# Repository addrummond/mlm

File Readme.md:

# Mimimalist Light Meter

## User manual

The user manual is [here](https://github.com/addrummond/mlm/blob/master/manual/manual.md).

## Overview

This is a simple ambient light meter using a Liteon LTR-303ALS light sensor and
an EFM32 Tiny Gecko ARM microcontroller. It is powered by a single CR2032 coin cell.
The firmware is written in C and the PCB is designed using KiCad. Readings are
displayed using a circle of 24 LEDs, with two additional LEDs indicating ±⅓ stop
adjustments. The user interface consists of three touch sensitive pads.

The goal of the project is to make available a simple, compact and inexpensive
light meter suitable for analogue photography. 

Dimensions: 87×56x7.5mm

The bottom side of the PCB (the side with no components mounted) is intended to
be used as the top panel of the case. This works best with a standard 1.6mm PCB
thickness.

The case is designed for 3D printing. It's best to use multi-jet fusion, as PLA
and ABS are usually not very light tight. (You could use PLA/ABS and then paint
the inside of the case black.) The STL file and Fusion 360 design for the case
are in the `case` directory. The PCB attaches to the case using five M1.6 4mm
countersunk screws. The dimples under the LEDs should be painted white and then
given a gloss varnish. A 10×10×2mm piece of transparent acrylic should be glued
in place over the sensor window. (If you don't add this, adjust
`WINDOW_ATTENUATION_STOPS` in `config.h`.)

The device functions as a reflective light meter. The same design could be
adapted for a spot meter or incident light meter by placing a lens or diffuser
over the sensor.

The LTR-303ALS integrates over a period of 50-400ms, which is far too long for
effective flash metering. A different design would therefore be required for
this purpose (probably using a discrete photodiode).

## Build notes

See `firmware/Readme.md` for notes on the dev toolchain.

Note that a recent (as of June 2020) development version of KiCad will be
required to open the board and schema files. Version 5.99.0-3928-g3c8396cd0 is
known to work. Each component in the schematic has a `MAN` (manufacturer) and
`MPN` (manufacturer part number) property.

I recommend using the [interactive BOM](https://github.com/openscopeproject/InteractiveHtmlBom) plugin for KiCad to aid manual placement of components.

## Known issue

* LEDs a little dim in bright daylight.

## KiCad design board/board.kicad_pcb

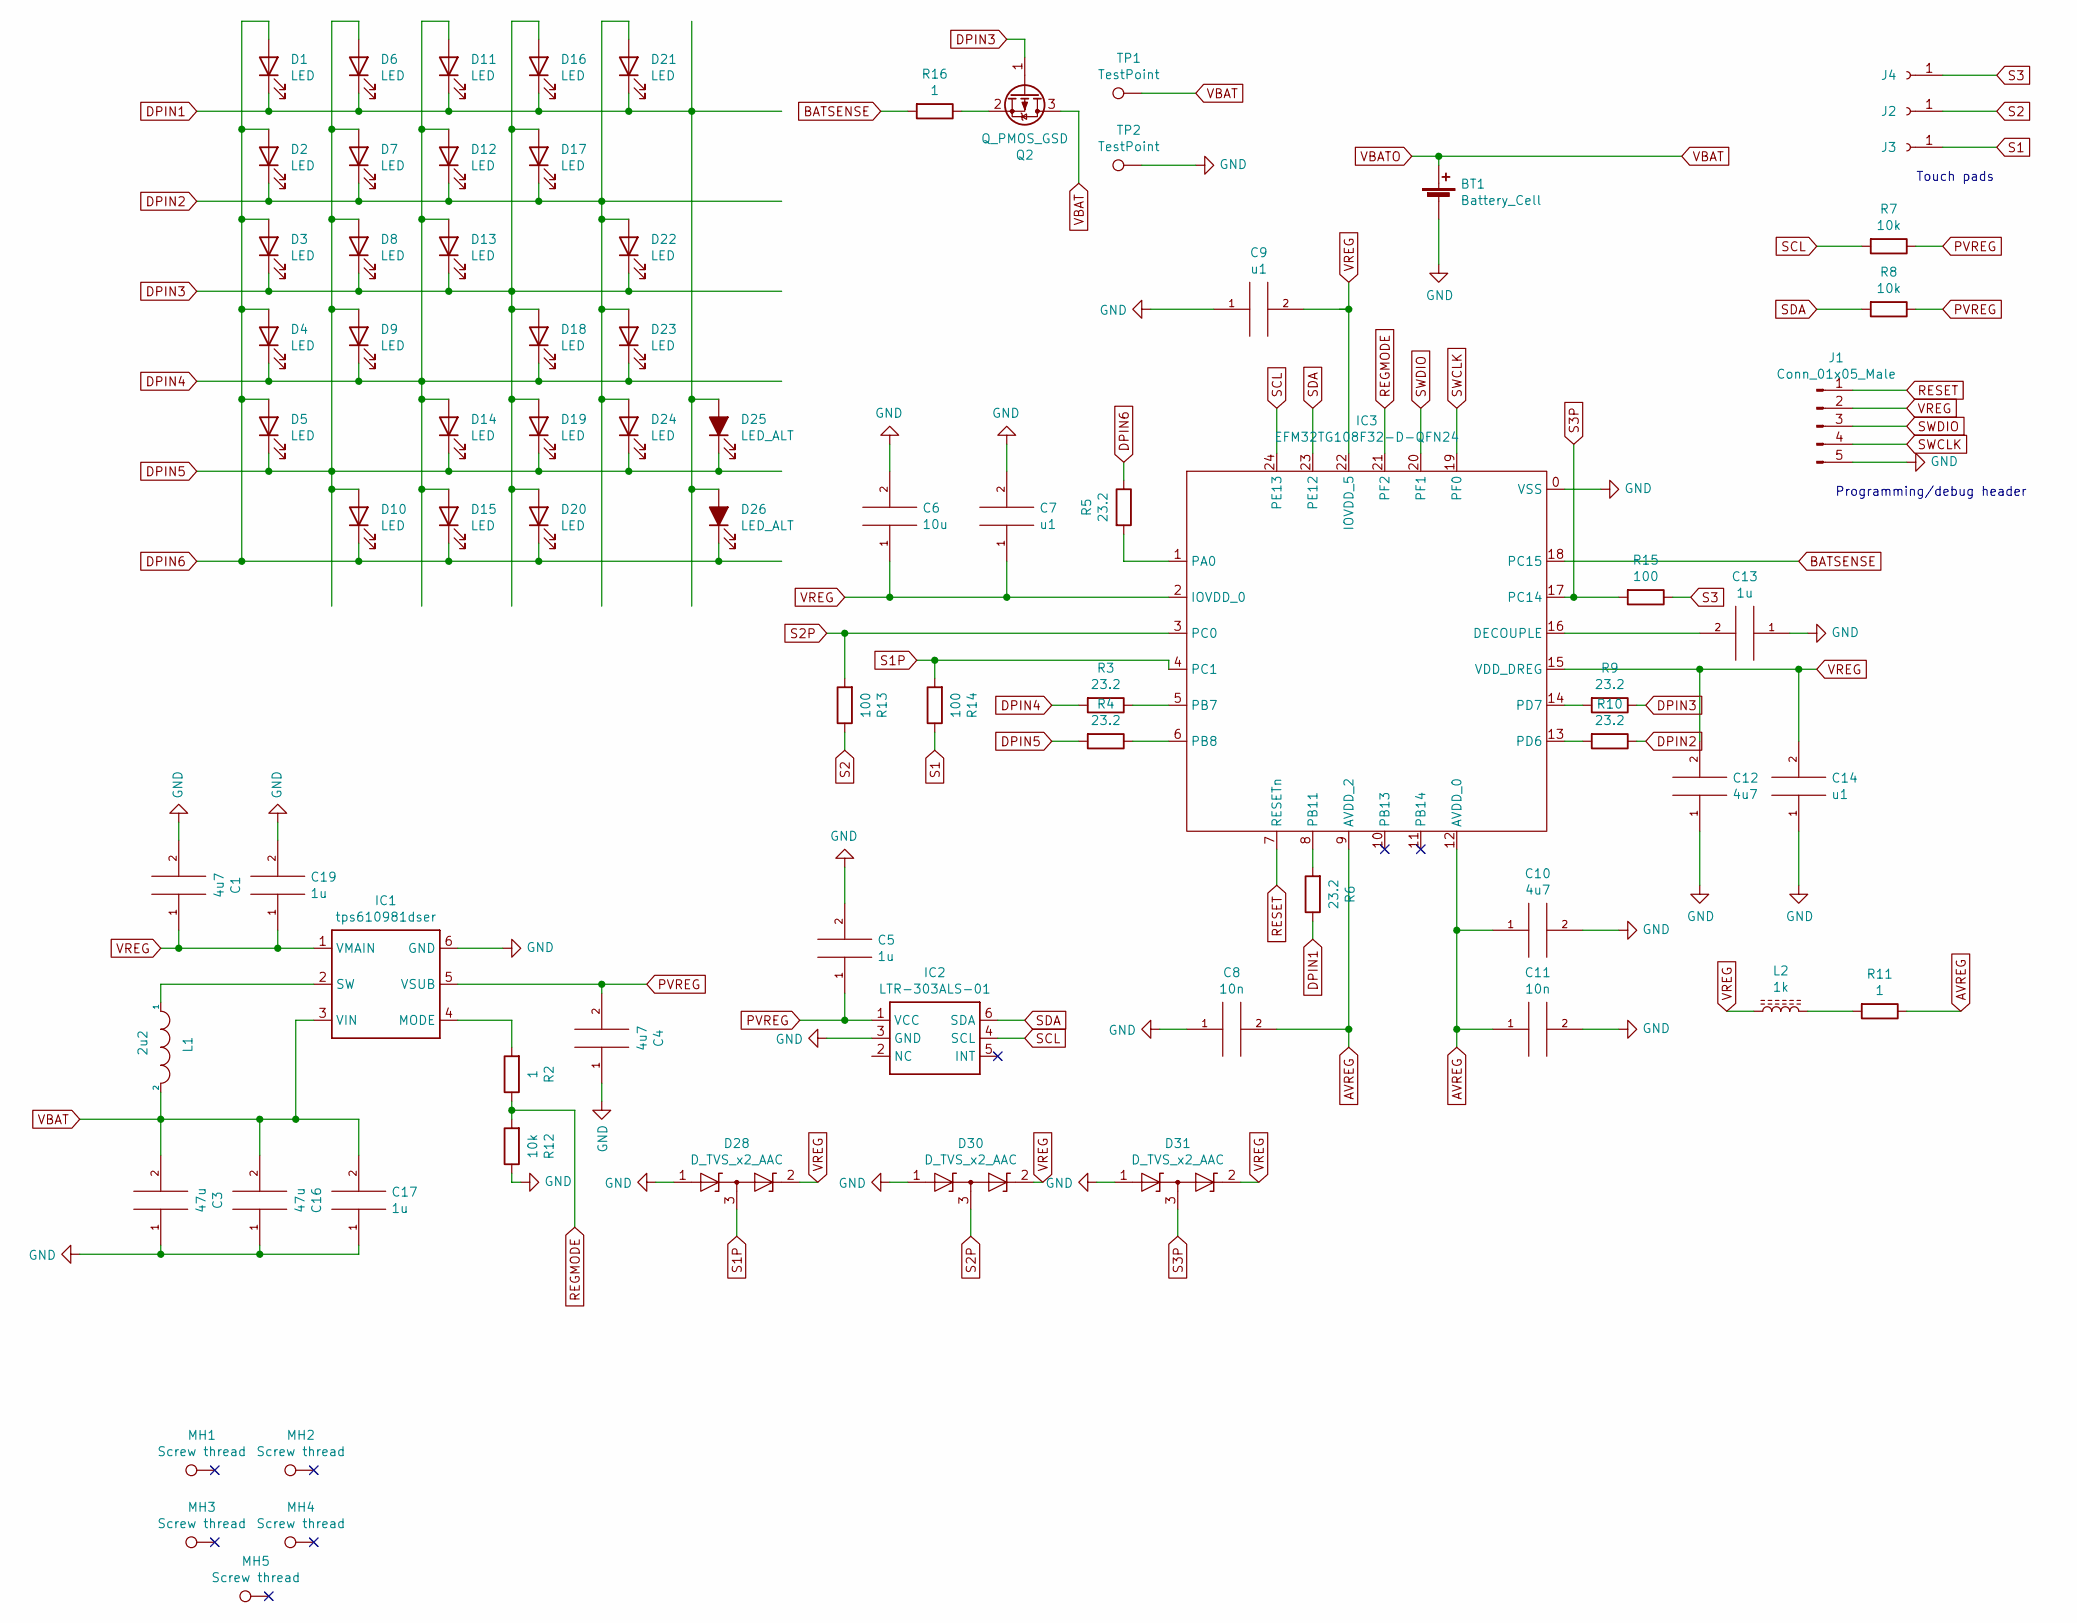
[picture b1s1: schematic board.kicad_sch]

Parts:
BT1: Battery_Cell; BK-5067; MPN BK-5067
C1, C4, C10, C12: 4u7; 0603; MPN C0603C475K9PAC7411
C3, C16: 47u; 0603; MPN GRM188R60G476ME15D
C5, C13, C17, C19: 1u; 0603; MPN CL10B105KP8NNNC
C6: 10u; 0603; MPN JMK107ABJ106MA-T
C7, C9, C14: u1; 0603; MPN 885012206020
C8, C11: 10n; 0603; MPN CL10B103KB8NNNC
D1, D2, D3, D4, D5, D6, D7, D8, D9, D10, D11, D12, D13, D14, D15, D16, D17, D18, D19, D20, D21, D22, D23, D24: LED; dual0402; MPN IN-S42BT5B
D25, D26: LED_ALT; dual0402; MPN IN-S42BT5B
D28, D30, D31: D_TVS_x2_AAC; SOT-23; MPN BAS70-04-TP
IC1: tps610981dser; tps610986; MPN TPS610981DSER
IC2: LTR-303ALS-01; LTR303ALS01; MPN LTR-303ALS-01
IC3: EFM32TG108F32-D-QFN24; EFM32TG108_QFN24; MPN EFM32TG108F32-QFN24
J1: Conn_01x05_Male; M20-7910542R; MPN M20-7910542R
J2, J3, J4: TOUCHPAD
L1: 2u2; NRS4010T2R2MDGG; MPN NRS4010T2R2MDGG
L2: 1k; 0805; MPN BLM21BD102SN1D
MH1, MH2, MH3, MH4, MH5: Screw thread; 97730306330R; MPN 97730306330R
Q2: Q_PMOS_GSD; SOT-23; MPN SI2329DS-T1-GE3
R2, R11, R16: 1; 0603; MPN ERJ3RQF1R0V
R3, R4, R5, R6, R9, R10: 23.2; 0603; MPN ERJ-3EKF23R2V
R7, R8, R12: 10k; 0603; MPN RNCP0603FTD10K0
R13, R14, R15: 100; 0603; MPN RC0603FR-07100RL
TP1, TP2: TestPoint; TestPoint_Pad_D1.5mm

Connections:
AVREG: C8.2, C10.1, C11.1, IC3.9 (AVDD_2), IC3.12 (AVDD_0), R11.1
BATSENSE: IC3.18 (PC15), R16.2
DPIN1: D1.1 (K), D6.1 (K), D11.1 (K), D16.1 (K), D21.1 (K), D25.2 (A), D26.2 (A), R6.1
DPIN2: D2.1 (K), D7.1 (K), D12.1 (K), D17.1 (K), D21.2 (A), D22.2 (A), D23.2 (A), D24.2 (A), R10.1
DPIN3: D3.1 (K), D8.1 (K), D13.1 (K), D16.2 (A), D17.2 (A), D18.2 (A), D19.2 (A), D20.2 (A), D22.1 (K), Q2.1 (G), R9.1
DPIN4: D4.1 (K), D9.1 (K), D11.2 (A), D12.2 (A), D13.2 (A), D14.2 (A), D15.2 (A), D18.1 (K), D23.1 (K), R3.2
DPIN5: D5.1 (K), D6.2 (A), D7.2 (A), D8.2 (A), D9.2 (A), D10.2 (A), D14.1 (K), D19.1 (K), D24.1 (K), D25.1 (K), R4.2
DPIN6: D1.2 (A), D2.2 (A), D3.2 (A), D4.2 (A), D5.2 (A), D10.1 (K), D15.1 (K), D20.1 (K), D26.1 (K), R5.1
GND: BT1.2 (-), C1.2, C3.1, C4.1, C5.2, C6.2, C7.2, C8.1, C9.1, C10.2, C11.2, C12.1, C13.1, C14.1, C16.1, C17.1, C19.2, D28.1 (A1), D30.1 (A1), D31.1 (A1), IC1.6 (GND), IC2.3 (GND), IC3.0 (VSS), J1.5, R12.1, TP2.1
unnamed: C13.2, IC3.16 (DECOUPLE)
unnamed: IC1.2 (SW), L1.1
unnamed: IC1.4 (MODE), R2.2
unnamed: IC3.1 (PA0), R5.2
unnamed: IC3.5 (PB7), R3.1
unnamed: IC3.6 (PB8), R4.1
unnamed: IC3.8 (PB11), R6.2
unnamed: IC3.13 (PD6), R10.2
unnamed: IC3.14 (PD7), R9.2
unnamed: L2.2, R11.2
unnamed: Q2.2 (S), R16.1
PVREG: C4.2, C5.1, IC1.5 (VSUB), IC2.1 (VCC), R7.1, R8.1
REGMODE: IC3.21 (PF2), R2.1, R12.2
RESET: IC3.7 (RESETn), J1.1
S1: J3.1, R14.1
S1P: D28.3 (common), IC3.4 (PC1), R14.2
S2: J2.1, R13.1
S2P: D30.3 (common), IC3.3 (PC0), R13.2
S3: J4.1, R15.1
S3P: D31.3 (common), IC3.17 (PC14), R15.2
SCL: IC2.4 (SCL), IC3.24 (PE13), R7.2
SDA: IC2.6 (SDA), IC3.23 (PE12), R8.2
SWCLK: IC3.19 (PF0), J1.4
SWDIO: IC3.20 (PF1), J1.3
VBAT: BT1.1 (+), C3.2, C16.2, C17.2, IC1.3 (VIN), L1.2, Q2.3 (D), TP1.1
VREG: C1.1, C6.1, C7.1, C9.2, C12.2, C14.2, C19.1, D28.2 (A2), D30.2 (A2), D31.2 (A2), IC1.1 (VMAIN), IC3.2 (IOVDD_0), IC3.15 (VDD_DREG), IC3.22 (IOVDD_5), J1.2, L2.1

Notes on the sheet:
Programming/debug header
Touch pads

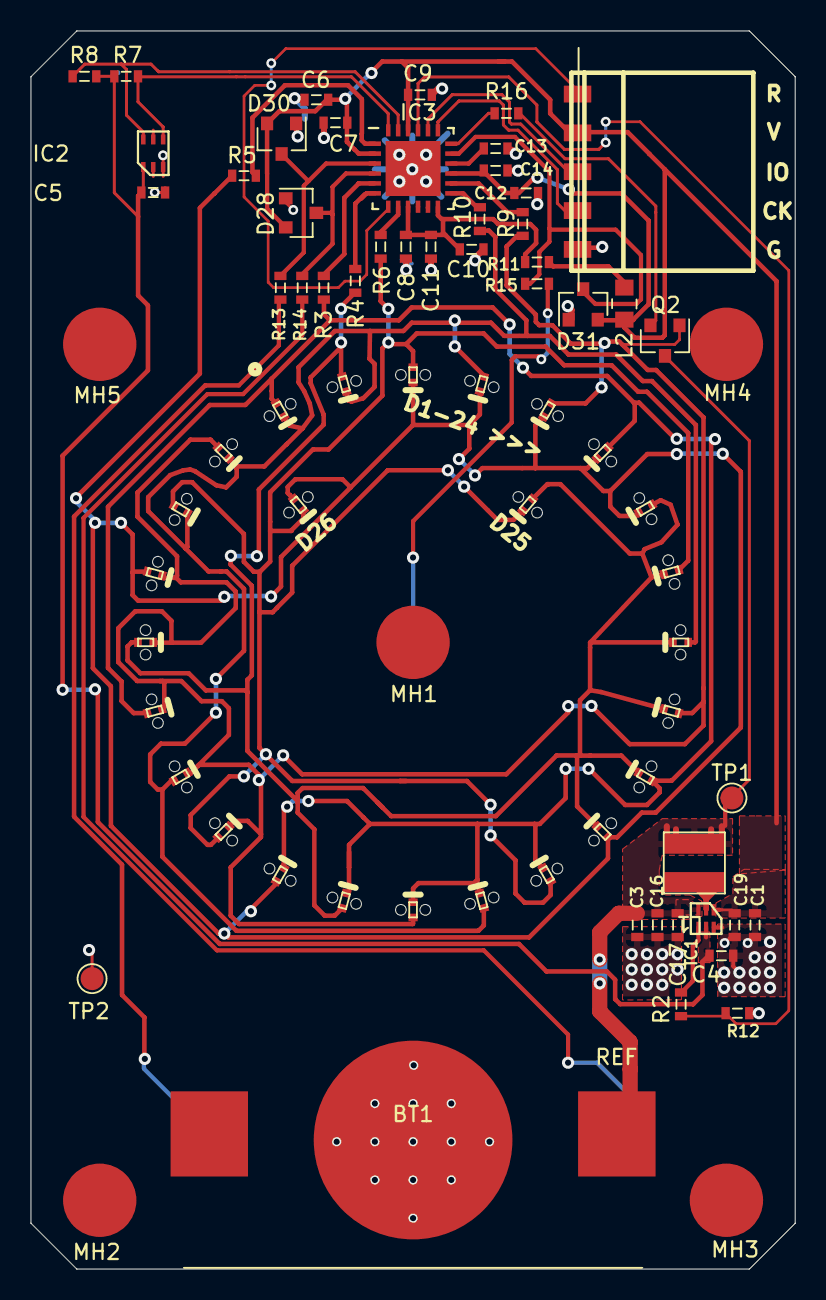
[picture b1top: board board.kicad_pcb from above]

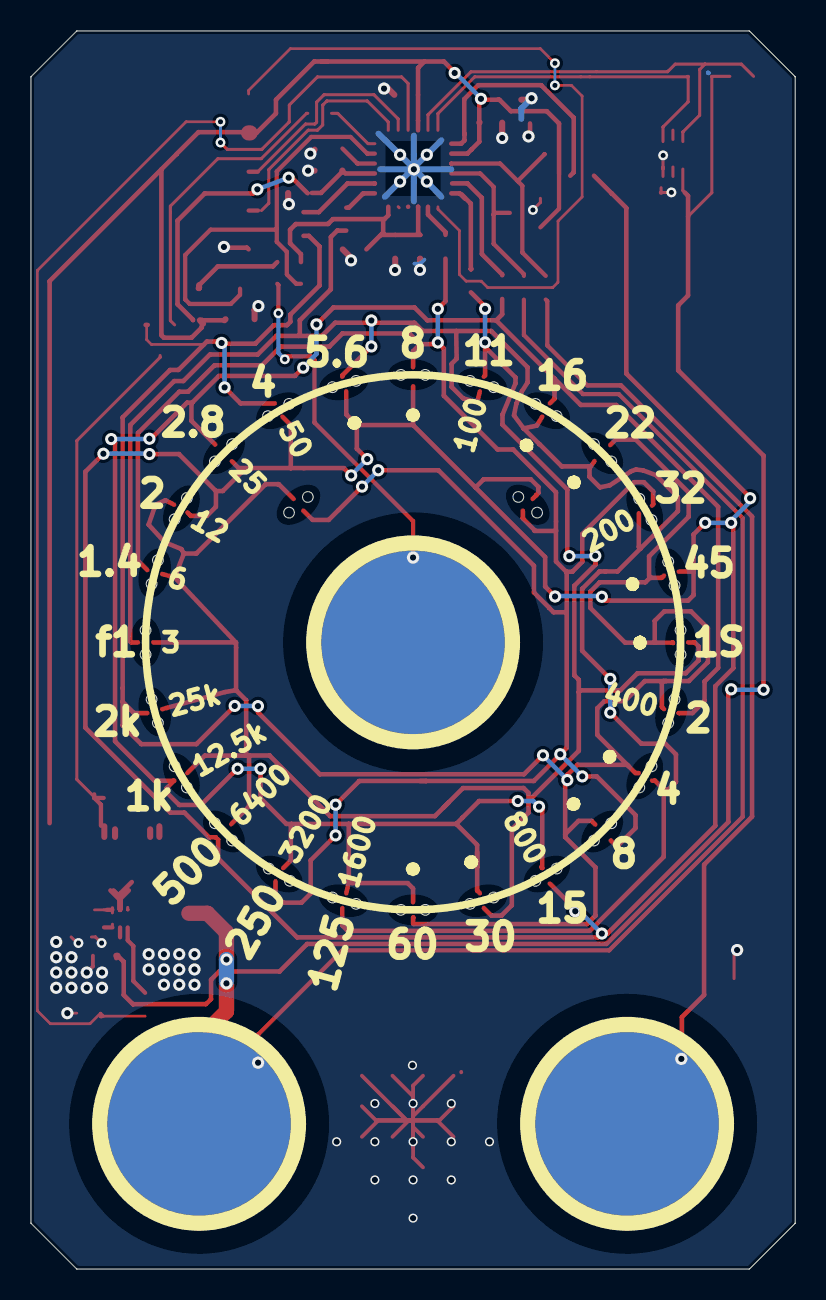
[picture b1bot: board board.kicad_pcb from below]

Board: 2 copper layers, 50.0 x 81.0 mm, 78 parts (29 on the bottom side), 35 nets.

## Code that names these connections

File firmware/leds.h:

#ifndef LEDS_HH
#define LEDS_HH

#include <stdbool.h>
#include <stdint.h>

#define LED_N           26
#define LED_N_IN_WHEEL  24

#define DPIN1_GPIO_PORT gpioPortB
#define DPIN1_GPIO_PIN  11
#define DPIN1_TIMER     TIMER1
#define DPIN1_CHAN      2
#define DPIN1_ROUTE     TIMER_ROUTE_CC2PEN
#define DPIN1_LOCATION  TIMER_ROUTE_LOCATION_LOC3

#define DPIN2_GPIO_PORT gpioPortD
#define DPIN2_GPIO_PIN  6
#define DPIN2_TIMER     TIMER1
#define DPIN2_CHAN      0
#define DPIN2_ROUTE     TIMER_ROUTE_CC0PEN
#define DPIN2_LOCATION  TIMER_ROUTE_LOCATION_LOC4

#define DPIN3_GPIO_PORT gpioPortD
#define DPIN3_GPIO_PIN  7
#define DPIN3_TIMER     TIMER1
#define DPIN3_CHAN      1
#define DPIN3_ROUTE     TIMER_ROUTE_CC1PEN
#define DPIN3_LOCATION  TIMER_ROUTE_LOCATION_LOC4

#define DPIN4_GPIO_PORT gpioPortB
#define DPIN4_GPIO_PIN  7
#define DPIN4_TIMER     TIMER1
#define DPIN4_CHAN      0
#define DPIN4_ROUTE     TIMER_ROUTE_CC0PEN
#define DPIN4_LOCATION  TIMER_ROUTE_LOCATION_LOC3

#define DPIN5_GPIO_PORT gpioPortB
#define DPIN5_GPIO_PIN  8
#define DPIN5_TIMER     TIMER1
#define DPIN5_CHAN      1
#define DPIN5_ROUTE     TIMER_ROUTE_CC1PEN
#define DPIN5_LOCATION  TIMER_ROUTE_LOCATION_LOC3

#define DPIN6_GPIO_PORT gpioPortA
#define DPIN6_GPIO_PIN  0
#define DPIN6_TIMER     TIMER0
#define DPIN6_CHAN      0
#define DPIN6_ROUTE     TIMER_ROUTE_CC0PEN
#define DPIN6_LOCATION  TIMER_ROUTE_LOCATION_LOC0

#ifndef LEDS_WRONG_WAY_ROUND
#define LED1_CAT_DPIN   1
#define LED2_CAT_DPIN   2
#define LED3_CAT_DPIN   3
#define LED4_CAT_DPIN   4
#define LED5_CAT_DPIN   5
#define LED6_CAT_DPIN   1
#define LED7_CAT_DPIN   2
#define LED8_CAT_DPIN   3
#define LED9_CAT_DPIN   4
#define LED10_CAT_DPIN  6
#define LED11_CAT_DPIN  1
#define LED12_CAT_DPIN  2
#define LED13_CAT_DPIN  3
#define LED14_CAT_DPIN  5
#define LED15_CAT_DPIN  6
#define LED16_CAT_DPIN  1
#define LED17_CAT_DPIN  2
#define LED18_CAT_DPIN  4
#define LED19_CAT_DPIN  5
#define LED20_CAT_DPIN  6
#define LED21_CAT_DPIN  1
#define LED22_CAT_DPIN  3
#define LED23_CAT_DPIN  4
#define LED24_CAT_DPIN  5
#define LED25_CAT_DPIN  5
#define LED26_CAT_DPIN  6
#define LED1_AN_DPIN    6
#define LED2_AN_DPIN    6
#define LED3_AN_DPIN    6
#define LED4_AN_DPIN    6
#define LED5_AN_DPIN    6
#define LED6_AN_DPIN    5
#define LED7_AN_DPIN    5
#define LED8_AN_DPIN    5
#define LED9_AN_DPIN    5
#define LED10_AN_DPIN   5
#define LED11_AN_DPIN   4
#define LED12_AN_DPIN   4
#define LED13_AN_DPIN   4
#define LED14_AN_DPIN   4
#define LED15_AN_DPIN   4
#define LED16_AN_DPIN   3
#define LED17_AN_DPIN   3
#define LED18_AN_DPIN   3
#define LED19_AN_DPIN   3
#define LED20_AN_DPIN   3
#define LED21_AN_DPIN   2
#define LED22_AN_DPIN   2
#define LED23_AN_DPIN   2
#define LED24_AN_DPIN   2
#define LED25_AN_DPIN   1
#define LED26_AN_DPIN   1
#else
#define LED1_AN_DPIN   1
#define LED2_AN_DPIN   2
#define LED3_AN_DPIN   3
#define LED4_AN_DPIN   4
#define LED5_AN_DPIN   5
#define LED6_AN_DPIN   1
#define LED7_AN_DPIN   2
#define LED8_AN_DPIN   3
#define LED9_AN_DPIN   4
#define LED10_AN_DPIN  6
#define LED11_AN_DPIN  1
#define LED12_AN_DPIN  2
#define LED13_AN_DPIN  3
#define LED14_AN_DPIN  5
#define LED15_AN_DPIN  6
#define LED16_AN_DPIN  1
#define LED17_AN_DPIN  2
#define LED18_AN_DPIN  4
#define LED19_AN_DPIN  5
#define LED20_AN_DPIN  6
#define LED21_AN_DPIN  1
#define LED22_AN_DPIN  3
#define LED23_AN_DPIN  4
#define LED24_AN_DPIN  5
#define LED25_AN_DPIN  5
#define LED26_AN_DPIN  6
#define LED1_CAT_DPIN    6
#define LED2_CAT_DPIN    6
#define LED3_CAT_DPIN    6
#define LED4_CAT_DPIN    6
#define LED5_CAT_DPIN    6
#define LED6_CAT_DPIN    5
#define LED7_CAT_DPIN    5
#define LED8_CAT_DPIN    5
#define LED9_CAT_DPIN    5
#define LED10_CAT_DPIN   5
#define LED11_CAT_DPIN   4
#define LED12_CAT_DPIN   4
#define LED13_CAT_DPIN   4
#define LED14_CAT_DPIN   4
#define LED15_CAT_DPIN   4
#define LED16_CAT_DPIN   3
#define LED17_CAT_DPIN   3
#define LED18_CAT_DPIN   3
#define LED19_CAT_DPIN   3
#define LED20_CAT_DPIN   3
#define LED21_CAT_DPIN   2
#define LED22_CAT_DPIN   2
#define LED23_CAT_DPIN   2
#define LED24_CAT_DPIN   2
#define LED25_CAT_DPIN   1
#define LED26_CAT_DPIN   1
#endif

#define LED_FOR_EACH(m) m(1) m(2) m(3) m(4) m(5) m(6) m(7) m(8) m(9) m(10) m(11) m(12) m(13) m(14) m(15) m(16) m(17) m(18) m(19) m(20) m(21) m(22) m(23) m(24) m(25) m(26)

#define DPIN_FOR_EACH(m) m(1) m(2) m(3) m(4) m(5) m(6)

#define LED_ISO6_N      18
#define LED_F8_N        0
#define LED_F11_N       1
#define LED_F16_N       2
#define LED_F22_N       3
#define LED_F32_N       4
#define LED_F45_N       5
#define LED_1S_N        6
#define LED_2_N         7
#define LED_4_N         8
#define LED_8_N         9
#define LED_15_N        10
#define LED_30_N        11
#define LED_60_N        12
#define LED_125_N       13
#define LED_250_N       14
#define LED_500_N       15
#define LED_1000_N      16
#define LED_2000_N      17
#define LED_F1_N        18
#define LED_F1_4_N      19
#define LED_F2_N        20
#define LED_F2_8_N      21
#define LED_F4_N        22
#define LED_F5_6_N      23
#define LED_MINUS_1_3_N 24
#define LED_PLUS_1_3_N  25

#define LED_OUT_OF_RANGE_MASK 0b100000000000000000000011

void reset_led_state();
void leds_on(uint32_t mask);
void leds_change_mask(uint32_t mask);
void leds_all_off();
uint32_t led_mask_for_reading(int ap_index, int ss_index, int third);
void set_led_throb_mask(uint32_t mask);
void set_led_flash_mask(uint32_t mask);
bool rtc_borked_for_led_cycling(void);

extern volatile uint32_t leds_on_for_cycles;

#endif

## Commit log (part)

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2020-04-09 fix syntax error in efm32/load.ld
2020-04-10 initial work on using EM3 deep sleep
2020-04-10 fix some counter overflow bugs
2020-04-10 fix some DEBUG/TEST and sleep mode mixups
2020-04-10 TEMP
2020-04-10 Add manual
2020-04-21 fix counter bug
2020-04-21 Get calibration wakeup working again
2020-04-21 further incomplete work on deep sleep
2020-04-21 fixes to reset test
2020-04-22 clean up code
2020-04-23 code style
2020-04-23 remove uninformative comments
2020-04-23 fix some bad timer count logic
2020-04-26 no vias near IC - potential for light leaks
2020-04-26 minor
2020-04-26 fix drc
2020-04-30 move temp sensor further from reflectors
2020-04-30 move resistors a little further from prog connector pads
2020-05-02 fix issues with deep sleep wakeup
2020-05-02 define GRACE_PERIOD_SECONDS
2020-05-02 add DEEP_SLEEP_TIMEOUT_SECONDS_DEBUG_MODE
2020-05-02 move some files to better locations
2020-05-02 move windownotes to more logical location
2020-05-02 initial work on better window FOV calcs
2020-05-02 more work on window calcs
2020-05-02 tweaks
2020-05-03 remove gotos
2020-05-03 flip sensor to landscape orientation
2020-05-03 tweak
2020-05-03 update config for new window size
2020-05-03 update manual with field of view
2020-05-03 update meter range in manual for smaller window
2020-05-03 Revert "remove gotos" (seems to have introduced subtle bugs)
    This reverts commit 7c52076fc39e1ca2944deef40f040b6ea77dc978.
2020-05-03 fix some touch count bugs
2020-05-03 TEMP sanity
2020-05-03 TEMP in middle of debugging
2020-05-03 TEMP MESS
2020-05-03 TEMP WEIRD
2020-05-03 TEMP MESS BEFORE PARAM
2020-05-03 number calls
2020-05-03 TEMP to undo
2020-05-03 Revert "TEMP to undo"
    This reverts commit 6aa3a39955cef314ba1b8bed490c1fb5ee76ddd0.
2020-05-03 experiment with cycle counter
2020-05-03 EXPERIMENTS WITH delay_count_cyc
2020-05-03 HMMMM
2020-05-03 REPRO PROB WITH SIMPL CODE
2020-05-03 REMOVE ENAB
2020-05-03 REMOVE unnecessary on/offing
2020-05-03 STILL MESSED UP
2020-05-04 Interesting results from disabling
2020-05-04 TEMP le capsense disable
2020-05-04 fix various touch count issues
2020-05-05 remove non-useful printfs
2020-05-05 more use of delay_ms_cyc
2020-05-05 oops
2020-05-05 manual update
2020-05-06 Add ADA4528-2 footprint
2020-05-07 initial work on ucurrent measurement option
2020-05-07 add board file in new format
2020-05-07 bigger pad for usb voltage
2020-05-07 remove old sch file
2020-05-07 work on ucurrent
2020-05-08 more ucurrent work
2020-05-08 use IC designator for op amp and LDO
2020-05-08 ger rid of stupid schematic border, as far as possible
2020-05-08 enter correct value for shunt resistor
2020-05-08 change iso scale
2020-05-08 fix angle of third LEDs and add arrows on silkscreen
2020-05-08 tweak silkscreen
2020-05-08 give up on third stop silkscreen
2020-05-08 JLCPCB order
2020-05-10 temp fix for nasty clock bug
2020-05-10 better fix for the CYCCNT bug
2020-05-10 count fix
2020-05-10 improve center press responsivity and remove duplicate function
2020-05-12 move resistor away from op amp ic
2020-05-13 add mpns
2020-05-13 various mpn and value changes
2020-05-14 stop using unnecessarily wide tracks
2020-05-15 minor tweaks to manual
2020-05-16 time compensation for touch counts
2020-05-16 Makefile syntax
2020-05-16 avoid some non-constant division with preprocessor lookup table
2020-05-16 remove unnecessary use of MACROUTILS_EVAL
2020-05-16 update resistor values in sim
2020-05-16 fix display of long shutter speeds
2020-05-16 Slightly reduce touch threshold
2020-05-17 Bug fix for spurious touch wakeup following watchdog reset
2020-05-17 remove unused variable
2020-05-17 use limited reset
2020-05-20 threshold tweak
2020-05-20 touch improvements
2020-05-21 fix slight misalignment of sensor
2020-05-21 add LEDS_WRONG_WAY_ROUND build option (lol)
2020-05-21 fix wrong mpn
2020-05-21 fix wrong mpns
2020-05-21 touch tweaks
2020-05-21 update iso logic for new iso dial labeling
2020-05-22 minor pcb tweaks
2020-05-22 sync board and sch
2020-05-22 give visual feedback when limits of wheel cycle reached
2020-05-22 remove some pointless debug prints
2020-05-22 minor board tweaks
2020-05-22 tweaks to manual
2020-05-23 remove dead code
2020-05-23 work on led code
2020-05-23 reduce unnecessarily high LED refresh rate
2020-05-23 remove debug test code
2020-05-23 major power consumption improvements
2020-05-23 fix watchdog reset regression
2020-05-24 more work reducing power consumption
2020-05-24 various tweaks
2020-05-24 this is already called by calibrate_le_capsense
2020-05-24 more debugging code
2020-05-24 use special functions to disable debug pins
2020-05-24 power saving work
2020-05-24 low energy work
2020-05-24 more low energy work
2020-05-24 remove measure delay
2020-05-26 remove some vias
2020-05-27 fix stupid circuit bug
2020-05-27 add wire pad for vshunt
2020-05-27 debugger stuff
2020-05-27 refactoring
2020-05-29 get DEBUG mode compiling again; add timing fudge factor
2020-05-30 accurate battery voltage measurements; put DPINs back to correct states
2020-05-30 fix typo
2020-05-30 increase cuteness
2020-05-30 add comment
2020-05-30 reduce computation
2020-05-30 tweak timing fudge factor
2020-05-30 use RAM storage for some speed/energy critical constants
2020-05-30 get rid of compiler warning
2020-05-30 add missing call to disable_capsense
2020-05-30 remove redundant code
2020-05-30 capsense pins can be left in disabled GPIO state at all times
2020-05-30 remove soldermask around LEDs on bottom layer
2020-05-30 correct mpns for 23.2 ohm resistors
2020-05-30 dial down left/right button sensitivity a little
2020-05-30 tweak touch handling
2020-05-31 store last ap
2020-05-31 use -Os for debug builds
2020-05-31 TEMP NOT BAD
2020-05-31 minor touch sensitivity tweak
2020-05-31 add note on calibration to manual
2020-05-31 work on manual
2020-05-31 bug fix
2020-05-31 minor touch tweak
2020-05-31 add Fusion 360 file for case
2020-05-31 updates to readme
2020-05-31 update to Readme
2020-05-31 add note on user manual
2020-05-31 tweak to manual
2020-05-31 touch tweak
2020-06-01 case update
2020-06-02 remove branch in interrupt handler
2020-06-03 attempt to deal better with interaction of interrupts and delay_ms_cyc
2020-06-06 more dev docs
2020-06-06 typo
2020-06-06 add STL file for case; add dimensions to Readme
2020-06-06 remove old py script that isn't being used
2020-06-06 add note on sensor window
2020-06-10 use DWT definition from official libs
2020-06-10 might need this on initial startup too
2020-06-10 remove delay_ms
2020-06-26 fix duty cycle logic
2020-06-27 remove wtf
2020-07-01 tweaks to touch handling
2020-07-01 datasheets dir is out of date and not much use; remove it
2020-07-01 more info on temp sensor and ucurrent
2020-07-01 add note
2020-07-01 Create LICENSE
2020-07-02 fix stupid logic bug with third stop indications
2020-07-02 add recent gerbers
2020-07-02 update gerbers
2020-07-04 Add MAN
2020-07-04 add missing MAN fields
2020-07-05 minor tweaks
2020-07-05 cheaper caps
2020-07-13 tidy up config.h
2020-07-17 Update LICENSE
2020-08-17 remove unnecesary cast
2020-08-17 tweak comment
2020-09-17 remove microcurrent
2020-09-17 minor tweaks to traces
2020-10-10 zone fill issues
2020-10-11 remove temp sensor
2020-10-11 use new inductor footprint
2020-10-11 TEMP BEFORE
2020-10-11 reduce led copper cutout size
2020-10-11 attempt to reduce total capacitance a little
2020-10-11 remove unused track
2020-10-11 minor layout tweak
2020-10-11 cut out bottom solder mask as well as copper layer over leds
2020-10-11 gnd fill tweaks
2020-10-11 make ramp up more gradual
2020-10-11 update reset_led_state
2020-10-11 add missing connection
2020-10-12 switch to using glider for battery holder
2020-10-12 more work on glider; cap changes
2020-10-12 silkscreen
2020-10-16 reduce ldo output cap
2020-12-08 fix some issues with keepout zone; stop via crossing shutter speed num
2020-12-08 jlcpcb order gerbers
2020-12-14 TEMP case changes
2020-12-16 fix some mpn metadata
2021-04-04 formatting
2021-04-04 remove no-longer-needed debug code
2021-04-04 disable deep sleep mode by default
2021-07-10 go back to higher led refresh
2021-07-10 fix code in test
2021-07-10 final tweaks to pcb
2021-07-10 inserting battery wrong way round could now potentially damage the meter
2021-07-10 board tweaks
2021-07-10 probably won't fix
2021-07-10 copy edit
2021-08-04 fix misplaced comment
2021-09-06 Update out of date comment
2021-11-03 change deep sleep logic
2021-11-03 Bump py from 1.8.1 to 1.10.0 in /case/fov
    Bumps [py](https://github.com/pytest-dev/py) from 1.8.1 to 1.10.0.
    - [Release notes](https://github.com/pytest-dev/py/releases)
    - [Changelog](https://github.com/pytest-dev/py/blob/master/CHANGELOG.rst)
    - [Commits](https://github.com/pytest-dev/py/compare/1.8.1...1.10.0)
    ---
    updated-dependencies:
2021-11-03 slow capsense scan period after a period of hours
2021-11-04 minor tweak to wakeup detection
2021-11-04 remove some unnecessary gotos
2021-11-04 tidy up real_main
2021-11-04 remove some debug logging that's no longer very useful
2021-11-05 fix arg order
2021-11-05 fix deep sleep bugs and add note to manual
2021-11-05 tweak scan hz
2021-11-05 indentation
2021-11-20 faster scan
2021-12-03 Revert "remove some unnecessary gotos"
    This reverts commit ab844dbc5f042ceeaff656e032a1d13a8df954d7.
2022-08-12 python deps
2022-08-12 fix logic bug in sleep
2022-11-23 remove pointless comment
